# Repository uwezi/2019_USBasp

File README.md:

# 2019_USBasp
2019 edition of a breadboard USBasp AVR programmer

This is just a quick upload place for my project around an USBasp AVR programmer 
based on the circuit used by Thomas Fischl, but easily placeable on a standard
breadboard.

The necessary gerber files for pcb manufacturing can be found in the folder "production"

A plan could be to merge the hardware layout with another firmware like
https://github.com/mariusgreuel/USBasp

The original firmware from Thomas Fischl can be used
https://www.fischl.de/usbasp/

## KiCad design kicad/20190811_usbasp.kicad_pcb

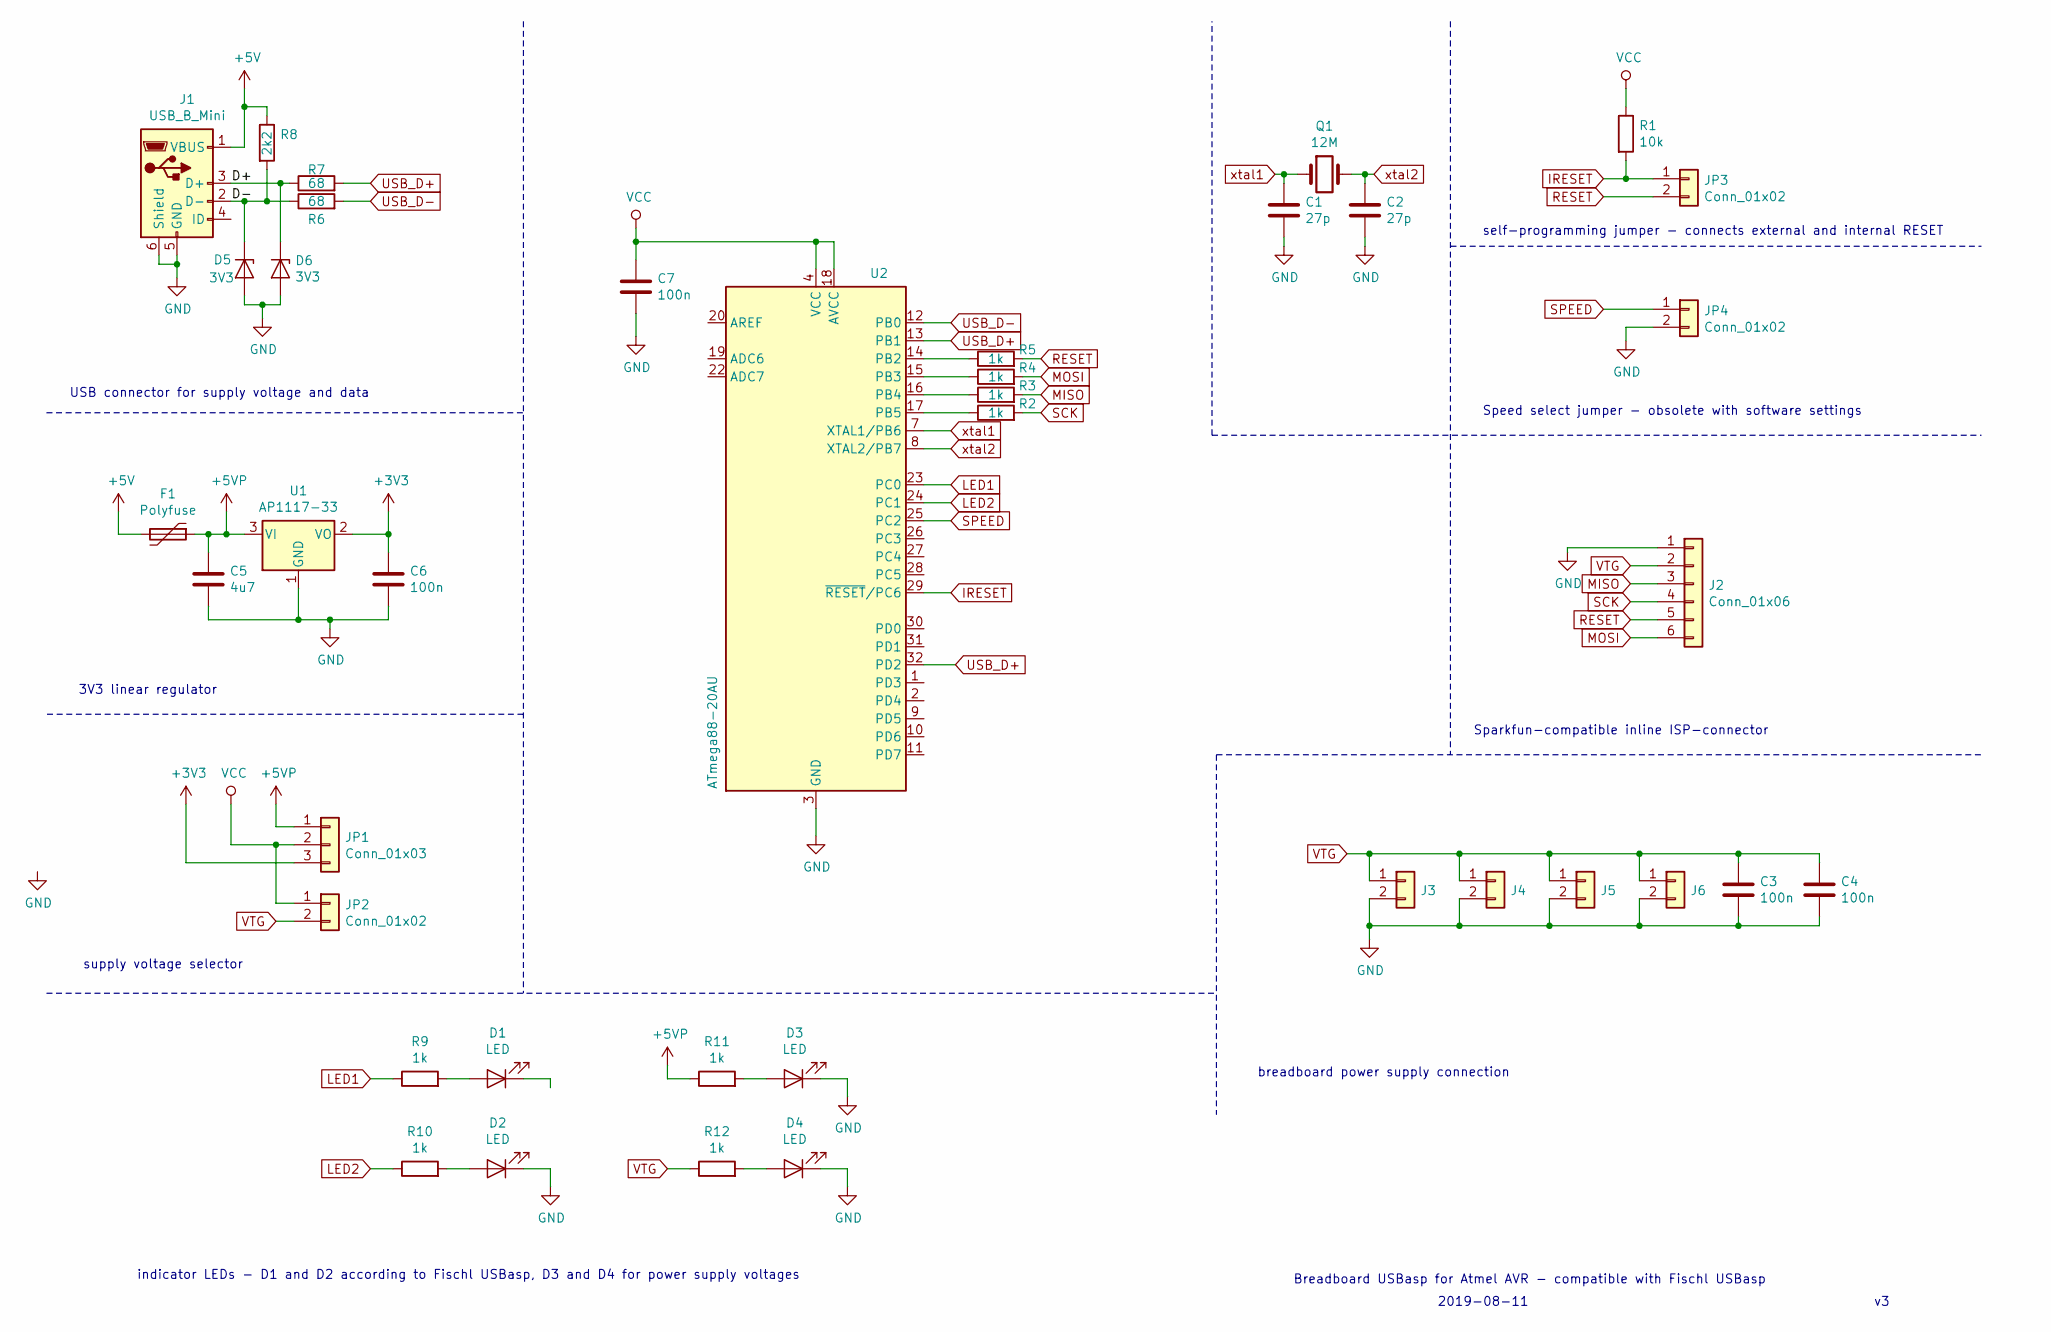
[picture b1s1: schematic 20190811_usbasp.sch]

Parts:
C1, C2: 27p; C_0805_2012Metric_Pad1.15x1.40mm_HandSolder
C3, C4, C6, C7: 100n; C_0805_2012Metric_Pad1.15x1.40mm_HandSolder
C5: 4u7; C_1206_3216Metric_Pad1.42x1.75mm_HandSolder
D1, D2, D3, D4: LED; LED_0805_2012Metric_Pad1.15x1.40mm_HandSolder
D5, D6: 3V3; D_MiniMELF
F1: Polyfuse; Fuse_2816_7142Metric
J1: USB_B_Mini; USB_Mini-B_Lumberg_2486_01_Horizontal
J2: Conn_01x06; PinSocket_1x06_P2.54mm_Vertical
J3, J4, J5, J6: Conn_01x02; PinHeader_1x02_P2.54mm_Vertical
JP1: Conn_01x03; PinHeader_1x03_P2.54mm_Vertical
JP2, JP3, JP4: Conn_01x02; PinHeader_1x02_P2.54mm_Vertical
Q1: 12M; Crystal_HC18-U_Vertical
R1: 10k; R_0805_2012Metric_Pad1.15x1.40mm_HandSolder
R2, R3, R4, R5, R9, R10, R11, R12: 1k; R_0805_2012Metric_Pad1.15x1.40mm_HandSolder
R6, R7: 68; R_0805_2012Metric_Pad1.15x1.40mm_HandSolder
R8: 2k2; R_0805_2012Metric_Pad1.15x1.40mm_HandSolder
U1: AP1117-33; SOT-223-3_TabPin2
U2: ATmega88-20AU; TQFP-32_7x7mm_P0.8mm

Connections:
+3V3: C6.1, JP1.3, U1.2 (VO)
+5V: F1.2, J1.1 (VBUS), R8.1
+5VP: C5.1, F1.1, JP1.1, R11.1, U1.3 (VI)
/D+: D6.1 (K), J1.3 (D+), R7.1
/D-: D5.1 (K), J1.2 (D-), R6.1, R8.2
GND: C1.2, C2.2, C3.2, C4.2, C5.2, C6.2, C7.2, D1.1 (K), D2.1 (K), D3.1 (K), D4.1 (K), D5.2 (A), D6.2 (A), J1.5 (GND), J1.6 (Shield), J2.1, J3.2, J4.2, J5.2, J6.2, JP4.2, U1.1 (GND), U2.3 (GND), U2.5 (GND), U2.21 (GND)
IRESET: JP3.1, R1.2, U2.29 (~RESET~/PC6)
LED1: R9.1, U2.23 (PC0)
LED2: R10.1, U2.24 (PC1)
MISO: J2.3, R3.2
MOSI: J2.6, R4.2
unnamed: D1.2 (A), R9.2
unnamed: D2.2 (A), R10.2
unnamed: D3.2 (A), R11.2
unnamed: D4.2 (A), R12.2
unnamed: R2.1, U2.17 (PB5)
unnamed: R3.1, U2.16 (PB4)
unnamed: R4.1, U2.15 (PB3)
unnamed: R5.1, U2.14 (PB2)
RESET: J2.5, JP3.2, R5.2
SCK: J2.4, R2.2
SPEED: JP4.1, U2.25 (PC2)
USB_D+: R7.2, U2.13 (PB1), U2.32 (PD2)
USB_D-: R6.2, U2.12 (PB0)
VCC: C7.1, JP1.2, JP2.1, R1.1, U2.4 (VCC), U2.6 (VCC), U2.18 (AVCC)
VTG: C3.1, C4.1, J2.2, J3.1, J4.1, J5.1, J6.1, JP2.2, R12.1
xtal1: C1.1, Q1.1, U2.7 (XTAL1/PB6)
xtal2: C2.1, Q1.2, U2.8 (XTAL2/PB7)

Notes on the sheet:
Speed select jumper - obsolete with software settings
self-programming jumper - connects external and internal RESET
Sparkfun-compatible inline ISP-connector
breadboard power supply connection
indicator LEDs - D1 and D2 according to Fischl USBasp, D3 and D4 for power supply voltages
supply voltage selector
3V3 linear regulator
USB connector for supply voltage and data
2019-08-11
Breadboard USBasp for Atmel AVR - compatible with Fischl USBasp

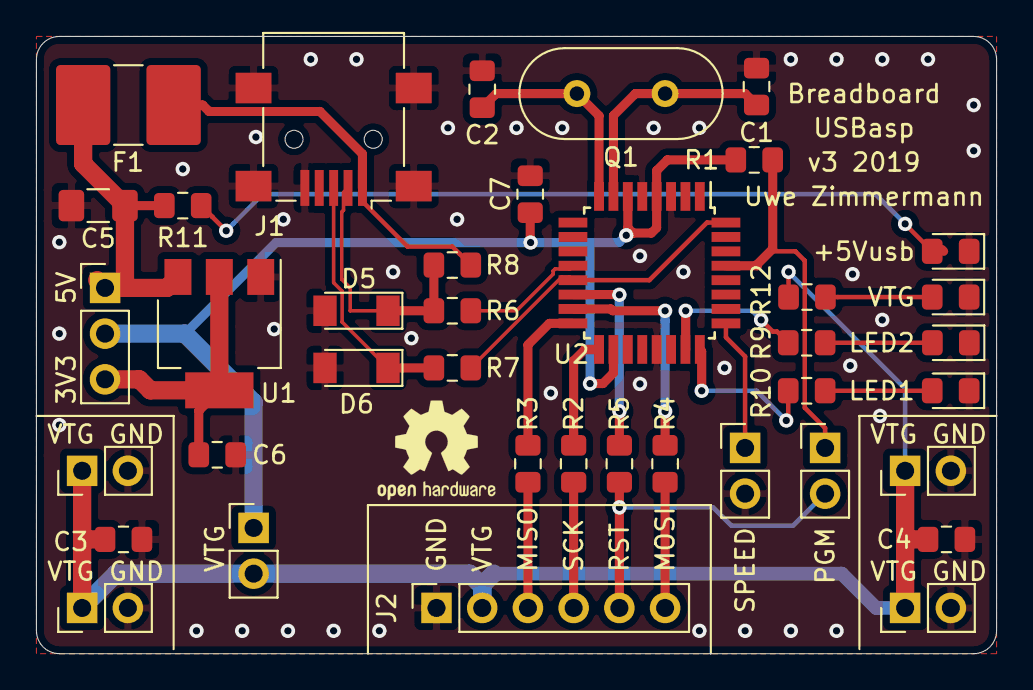
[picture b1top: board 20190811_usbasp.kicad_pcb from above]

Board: 2 copper layers, 53.3 x 34.3 mm, 39 parts (0 on the bottom side), 28 nets.

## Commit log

2022-07-05 Add files via upload
    kicad files
2022-07-05 Add files via upload
    ZIP archive with the Gerber files for production
